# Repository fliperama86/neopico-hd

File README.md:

# NeoPico-HD

Digital video and audio capture with HDMI output for Neo Geo MVS arcade hardware using Raspberry Pi Pico 2 (RP2350B).

## Features

- **Native 240p HDMI output** at 60fps (via 480p line doubling for audio compatibility)
- **Experimental exact-clock 720p HDMI output** - the normal selector uses a 64.000 MHz, 1440x741 reduced-blanking raster at 59.979 Hz and centers the source at 3x scale
- **15-bit RGB + SHADOW/DARK capture** - 19-bit capture path includes SHADOW and DARK control lines
- **Pixel Conversion Modes** - Stable 32K-entry RGB LUT, plus an optional live and persistent `Digital`/`Analog` normal-color selector that remains separate from DARK/SHADOW processing
- **Translucent OSD Panel** - Enabled by default; game pixels under the black panel retain 12.5% brightness while text and menu colors remain opaque
- **Digital audio capture** from I2S bus (before DAC) with 48kHz HDMI output
- **Zero-overhead DMA video capture** - uses PIO + DMA with ping-pong buffering for perfect stability
- **PicoHDMI Output** - Powered by the [PicoHDMI](https://github.com/fliperama86/pico_hdmi) library for efficient, hardware-native TMDS encoding via RP2350 HSTX.

## Status

| Feature                 | Status                                     |
| ----------------------- | ------------------------------------------ |
| 480p HDMI video         | Working                                    |
| 720p HDMI video         | Experimental (exact-clock runtime selector mode) |
| 60fps capture           | Working                                    |
| RGB555 Digital path     | Working                                    |
| Live Colors selector    | Available whenever DARK/SHADOW is off (MVS builds) |
| SHADOW/DARK capture     | Working                                    |
| SHADOW/DARK conversion  | Experimental, default off; split-LUT hardware test showed bottom-screen pixel jitter |
| HDMI audio (48kHz)      | Working                                    |
| OSD Diagnostics         | Working                                    |
| Morhph4K, RetroTink 4K  | Tested                                     |
| Samsung Q80, Acer Pred. | Tested                                     |

## Hardware Requirements

- **Raspberry Pi Pico 2** - Must be RP2350**B** variant (48 GPIOs) for digital audio capture
- **Neo Geo MVS board** - Tested on MV1C
- **HDMI connector** wired to Pico GPIO

### Hardware Setup & Signal Integrity

To ensure clean audio and video capture, follow these best practices:

1.  **Common Ground**: A solid ground connection between the MVS board and the Pico is **mandatory**.
2.  **HDMI Power**: It is **absolutely mandatory** to have the HDMI connector properly powered with **+5V**. While some devices (like the Morph4K) may be forgiving, others (like the RetroTINK, TVs and monitors) will not pick up the signal without it.
3.  **Level Shifting**: Route all MVS -> Pico digital lines through proper **5V-to-3.3V level shifters**.
4.  **Clock Conditioning**: Keep **Schmitt-trigger conditioning** on PCLK and BCK for clean edges.
5.  **Power-Path Isolation**: Prevent back-feed between external 5V and USB 5V (ideal diode/power mux approach recommended).
6.  **Cable Separation**: Physically separate the I2S audio wires (GPIO 22-24 path) from the video wire bundle to avoid coupling.
7.  **Shielding**: Use a **GND-Signal-GND** pattern when using ribbon cables.

### Pin Configuration

#### Video Capture (Bank 1)

| Function   | GPIO       | Notes                |
| ---------- | ---------- | -------------------- |
| MVS CSYNC  | GPIO 27    | Composite sync       |
| MVS PCLK   | GPIO 28    | 6 MHz pixel clock    |
| MVS Blue   | GPIO 29-33 | B4-B0 (contiguous)   |
| MVS Green  | GPIO 34-38 | G4-G0 (contiguous)   |
| MVS Red    | GPIO 39-43 | R4-R0 (contiguous)   |
| MVS SHADOW | GPIO 44    | Shadow dimming       |
| MVS DARK   | GPIO 45    | Dark dimming control |

#### HSTX Output (Bank 0/1)

| Function | GPIO       |
| -------- | ---------- |
| TMDS CLK | GPIO 12-13 |
| TMDS D0  | GPIO 14-15 |
| TMDS D1  | GPIO 16-17 |
| TMDS D2  | GPIO 18-19 |

#### Audio Capture

| Function | GPIO    | MV1C Tap Point |
| -------- | ------- | -------------- |
| I2S DAT  | GPIO 22 | R91            |
| I2S WS   | GPIO 23 | R90            |
| I2S BCK  | GPIO 24 | R92            |

#### Controller OSD Inputs (MVS/AES)

| Controller input | GPIO |
| ---------------- | ---- |
| START / MENU     | GP0  |
| SELECT / BACK    | GP1  |
| DOWN             | GP2  |
| UP               | GP3  |

The inputs are active low and use weak internal pull-ups so untapped pins stay
idle. They are always enabled, on both MVS/AES and SNES builds (GP0-3 are
unused by SNES capture, so this is harmless there too).

## Prebuilt Firmware

GitHub Releases include ready-to-flash selector firmware. Each UF2 can switch
between 240p, 480p, and 720p from the reboot-based OSD resolution menu. The MVS
asset also includes persistent Audio and live-preview Colors menus. The optional
PC monitor modes are default-off and are not included in those release choices.
The selector's 720p entry uses the exact 64.000 MHz reduced-blanking timing;
because it is non-CTA and advertises VIC 0, sink compatibility still needs broad
testing.

| Asset | Capture | OSD choices |
| ----- | ------- | ----------- |
| `neopico_hd_mvs.uf2` | Neo Geo MVS/AES | Resolution, Audio, and Digital/Analog Colors |
| `neopico_hd_snes.uf2` | SNES | Resolution |

Matching ELF files and the `neopico-hd-jlcpcb.zip` fabrication package are also
attached to each release. Controller-driven AES OSD navigation is enabled in
both release assets (GP0-3 are unused by SNES capture).

## Building

Requires [Pico SDK](https://github.com/raspberrypi/pico-sdk) with `PICO_SDK_PATH` set.

```bash
# Build and flash
./flash

# Optional standalone HDMI/OSD self-test firmware
cmake -S . -B build_selftest -DNEOPICO_BUILD_SELFTEST=ON
cmake --build build_selftest --target neopico_selftest -j4

# Standard MVS build. Audio is always SELECTABLE (persistent Audio menu
# between the digital NEO-YSA2 tap and an external PCM1802 ADC) and the
# live persistent Colors selector (Digital/Analog normal-color, ignoring
# DARK/SHADOW) is available automatically since DARK/SHADOW defaults off.
cmake -S . -B build_mvs
cmake --build build_mvs --target neopico_hd -j4

# Separate DARK/SHADOW timing experiment. This path produced bottom-screen
# pixel jitter in hardware testing. Enabling it automatically compiles out
# the Colors selector (the two features share the same capture LUT machinery).
cmake -S . -B build_effects \
  -DNEOPICO_ENABLE_DARK_SHADOW=ON \
  -DNEOPICO_MVS_EFFECT_MODEL=MISTER
cmake --build build_effects --target neopico_hd -j4

# Digital-only register-processing experiment. This replaces the split effect
# LUT with RBIT, bitfield, saturating DARK, and packed SHADOW operations. It is
# default off and must be hardware-validated before use in release firmware.
cmake -S . -B build_effects_processing \
  -DNEOPICO_COPY_TO_RAM=ON \
  -DNEOPICO_ENABLE_DARK_SHADOW=ON \
  -DNEOPICO_MVS_DIGITAL_EFFECT_PROCESSING=ON \
  -DNEOPICO_MVS_EFFECT_MODEL=MISTER
cmake --build build_effects_processing --target neopico_hd -j4
```

## Architecture

```
Core 0: Video Capture               Core 1: Audio Pipeline + HSTX
+--------------------------+       +--------------------------+
| Video: PIO1 -> DMA (PP)  |       | Audio: PIO2 -> processing|
| Conv: 32K LUT (dual opt) |       | [ PicoHDMI Library ]     |
| Main loop: Control       |       | - 640x480 @ 60Hz         |
| Heartbeat LED            |       | - HDMI Data Islands      |
+--------------------------+       +--------------------------+
          |                        +--------------------------+
          |                                   |
          +--------- framebuf ----------------+
                  (320x240 RGB565)
```

### PicoHDMI Library Integration

The project leverages the [PicoHDMI](https://github.com/fliperama86/pico_hdmi) library (found in `lib/pico_hdmi`) to interface with the RP2350's HSTX peripheral. This library provides the high-performance TMDS encoding and Data Island management required for stable HDMI output.

- **Dedicated Output Core**: To ensure rock-solid HDMI timing (exactly 800 cycles per line), the library runs its main loop on **Core 1**. This isolates the high-priority TMDS serialization from the video capture logic on Core 0.
- **Zero-Latency Scaling**: We use the library's `video_output_set_scanline_callback()` to implement a scanline doubler. This performs 2x vertical upscaling (240p to 480p) on-the-fly as pixels are streamed to the HSTX, avoiding the need for a full 480p framebuffer.
- **HDMI Audio Injection**: Audio data is integrated via the library's Data Island queue (`hstx_di_queue`). The audio subsystem pushes TERC4-encoded packets into this queue, which the library then automatically injects during the horizontal blanking intervals.
- **Frame Synchronization**: A VSYNC callback is used to keep the video capture ring buffer and the HDMI output in perfect sync, minimizing latency and preventing screen tearing.

## Documentation

- **[System Architecture](docs/ARCHITECTURE.md)**: High-level design, core partitioning, and the closed-loop audio sync.
- **[Video Implementation](docs/MVS_MV1C_DIGITAL_VIDEO.md)**: Tap points, signal logic, and PIO capture.
- **[Audio Implementation](docs/MVS_MV1C_DIGITAL_AUDIO.md)**: I2S format, ASRC strategy, and drift control.
- **[Standalone PCM1802 USB Capture](docs/PCM1802_USB_CAPTURE.md)**: Raw ADC diagnostic firmware and host capture tool.
- **[HSTX & HDMI](docs/HSTX_IMPLEMENTATION.md)**: Output timing, TMDS, and Data Islands.
- **[OSD](docs/OSD_IMPLEMENTATION.md)**: On-Screen Display rendering.
- **[Reboot Resolution Switching](docs/REBOOT_RESOLUTION_SWITCHING.md)**: Reboot selector modes.
- **[720p Samsung Game Mode Investigation](docs/720P_SAMSUNG_GAME_MODE_INVESTIGATION.md)**: Current findings on Samsung Game Mode 720p glitches.
- **[Known Issues](docs/KNOWN_ISSUES.md)**: Current limitations and compatibility notes.

## Architecture Highlights

- **Dual-Core Design**: Dedicated cores for Video Capture (Core 0) and HDMI Output (Core 1).
- **Closed-Loop Audio Sync**: Software-defined feedback loop effectively "genlocks" the MVS audio to the HDMI clock, preventing drift and glitches without an FPGA.
- **Zero-Lag**: Scanline-doubling architecture with no framebuffer delay.

## Installation

Unlicense

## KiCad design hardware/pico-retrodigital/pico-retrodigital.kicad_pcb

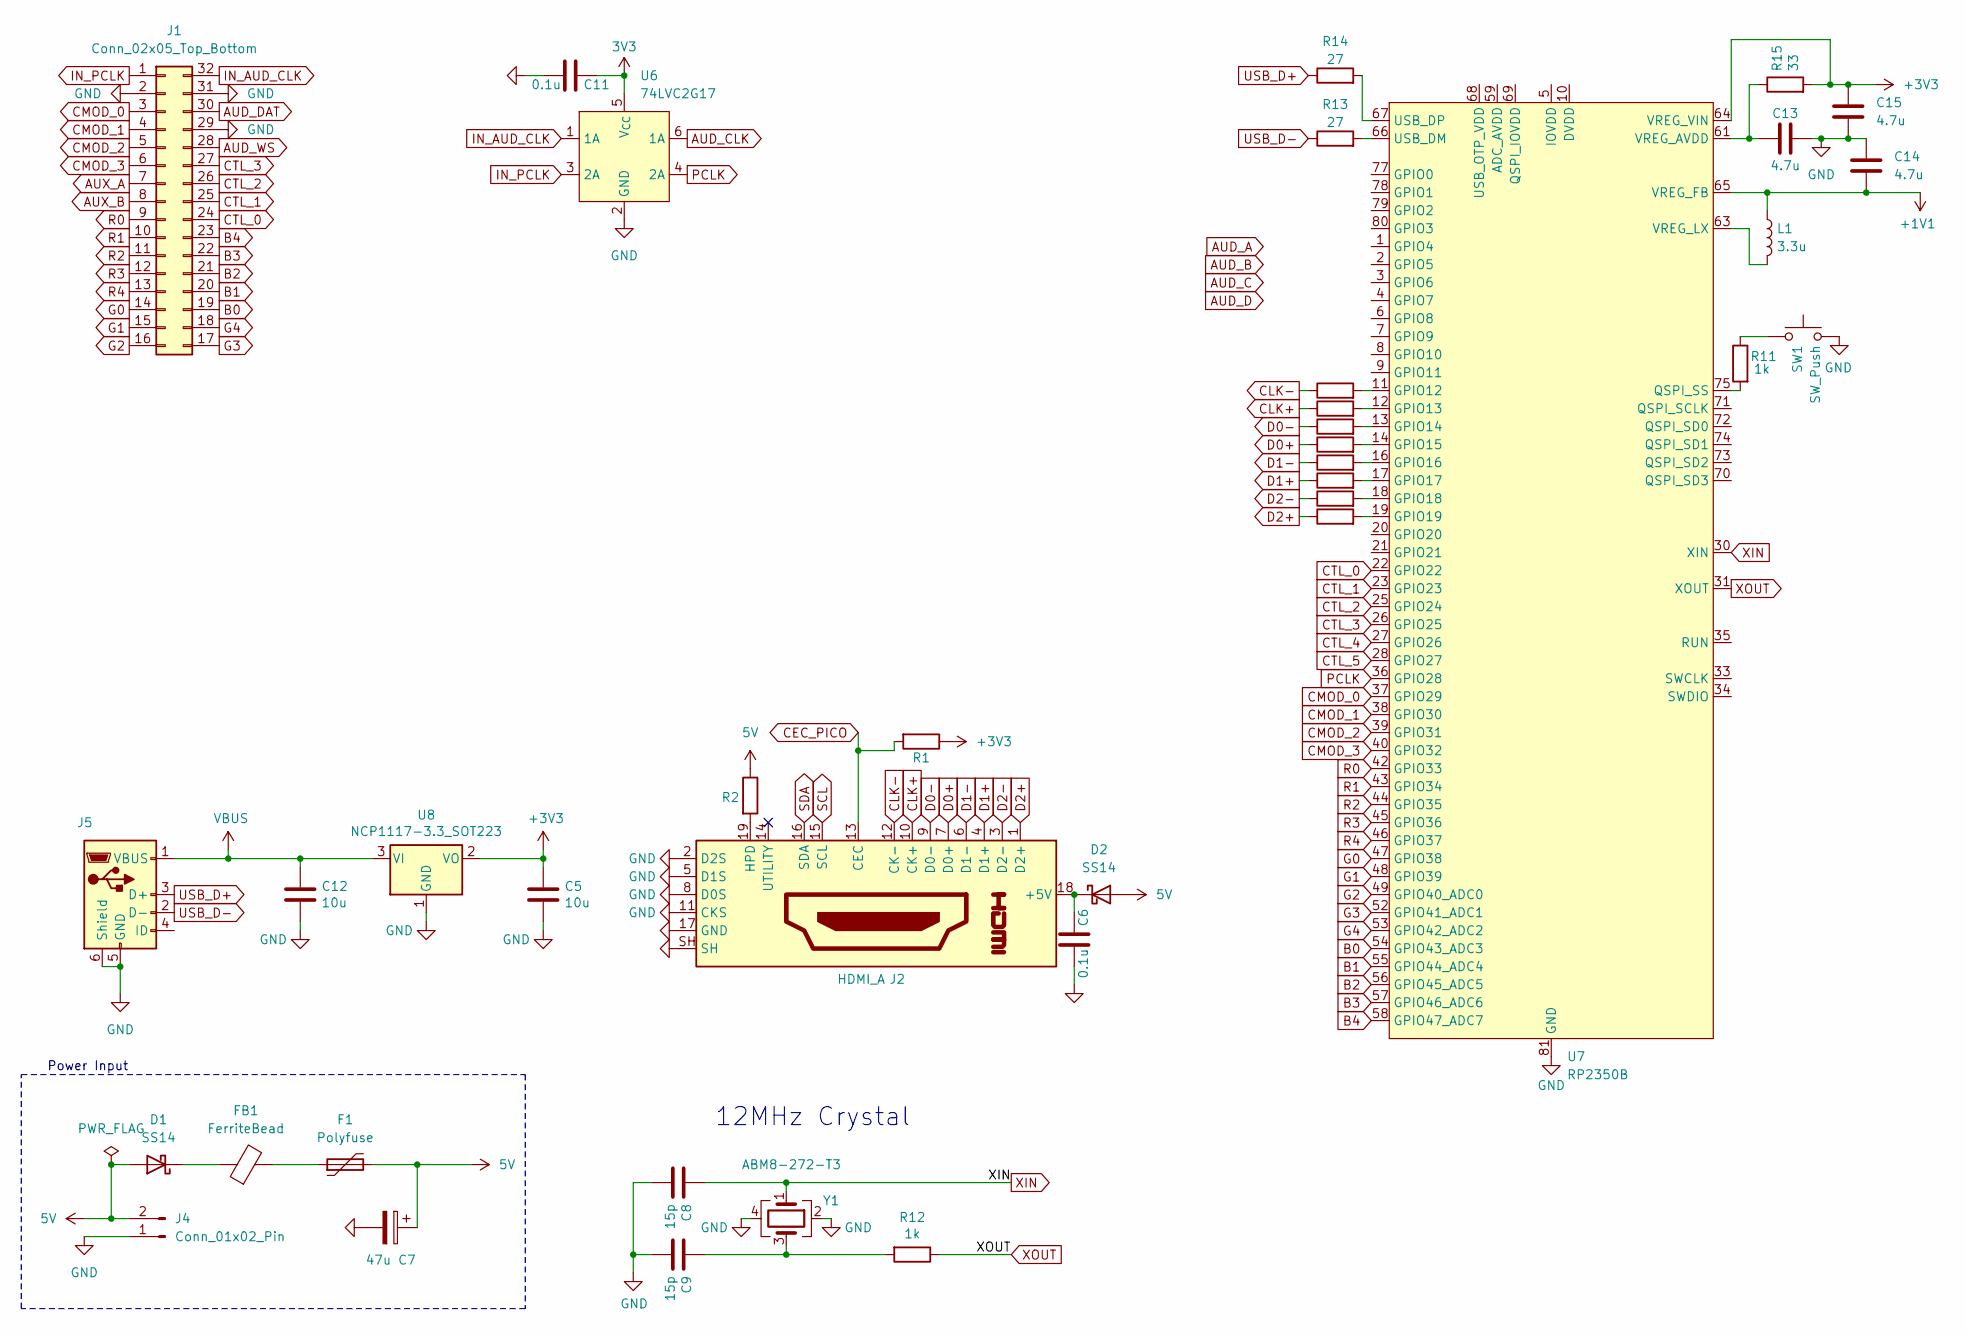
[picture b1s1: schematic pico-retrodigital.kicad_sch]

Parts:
C5, C12: 10u; C_0402_1005Metric
C6, C11: 0.1u; C_0603_1608Metric
C7: 47u; CP_Radial_D4.0mm_P2.00mm
C8, C9: 15p; C_0402_1005Metric
C13: 4.7u; C_0402_1005Metric
C14, C15: 4.7u; C_0402_1005Metric_small_pads
D1, D2: SS14; D_0603_1608Metric
F1: Polyfuse; C_0603_1608Metric
FB1: FerriteBead; C_0603_1608Metric
J1: Conn_02x05_Top_Bottom; TE_3-1734839-2_1x32-1MP_P0.5mm_Horizontal
J2: HDMI_A; HDMI_A_Molex_208658-1001_Horizontal
J4: Conn_01x02_Pin; PinHeader_1x02_P2.54mm_Vertical
J5: USB_C; USB_Micro-B_Amphenol_10103594-0001LF_Horizontal
L1: 3.3u; L_pol_2016
R1: 27K; R_0603_1608Metric
R2: 10K; R_0603_1608Metric
R3, R4, R5, R6, R7, R8, R9, R10: 220; R_0201_0603Metric
R11, R12: 1k; R_0402_1005Metric
R13, R14: 27; R_0402_1005Metric
R15: 33; R_0402_1005Metric
SW1: SW_Push; SW_Push_1P1T_NO_Vertical_Wuerth_434133025816
U6: 74LVC2G17; SOT-23-6
U7: RP2350B; QFN-80-1EP_10x10mm_P0.4mm_EP3.4x3.4mm_ThermalVias
U8: NCP1117-3.3_SOT223; SOT-223-3_TabPin2
Y1: ABM8-272-T3; Crystal_SMD_3225-4Pin_3.2x2.5mm

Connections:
3V3: C11.1, U6.5 (V_{CC})
5V: C7.1, D1.2 (A), D2.2 (A), F1.2, J4.2, R2.1
+1V1: C14.2, L1.1, U7.65 (VREG_FB)
+3V3: C5.1, C15.1, R1.1, R15.2, U7.64 (VREG_VIN), U8.2 (VO); also elsewhere on the board
AUD_CLK: U6.6 (1A)
AUD_DAT: J1.30
AUD_WS: J1.28
AUX_A: J1.7
AUX_B: J1.8
B0: J1.19, U7.54 (GPIO43_ADC3)
B1: J1.20, U7.55 (GPIO44_ADC4)
B2: J1.21, U7.56 (GPIO45_ADC5)
B3: J1.22, U7.57 (GPIO46_ADC6)
B4: J1.23, U7.58 (GPIO47_ADC7)
CEC_PICO: J2.13 (CEC), R1.2
CLK+: J2.10 (CK+), R5.1
CLK-: J2.12 (CK-), R4.1
CMOD_0: J1.3, U7.37 (GPIO29)
CMOD_1: J1.4, U7.38 (GPIO30)
CMOD_2: J1.5, U7.39 (GPIO31)
CMOD_3: J1.6, U7.40 (GPIO32)
CTL_0: J1.24, U7.22 (GPIO22)
CTL_1: J1.25, U7.23 (GPIO23)
CTL_2: J1.26, U7.25 (GPIO24)
CTL_3: J1.27, U7.26 (GPIO25)
CTL_4: U7.27 (GPIO26)
CTL_5: U7.28 (GPIO27)
D0+: J2.7 (D0+), R6.1
D0-: J2.9 (D0-), R3.1
D1+: J2.4 (D1+), R8.1
D1-: J2.6 (D1-), R7.1
D2+: J2.1 (D2+), R10.1
D2-: J2.3 (D2-), R9.1
G0: J1.14, U7.47 (GPIO38)
G1: J1.15, U7.48 (GPIO39)
G2: J1.16, U7.49 (GPIO40_ADC0)
G3: J1.17, U7.52 (GPIO41_ADC1)
G4: J1.18, U7.53 (GPIO42_ADC2)
GND: C5.2, C6.2, C7.2, C8.2, C9.2, C11.2, C12.2, C13.2, C14.1, C15.2, J1.2, J1.29, J1.31, J2.2 (D2S), J2.5 (D1S), J2.8 (D0S), J2.11 (CKS), J2.17 (GND), J2.SH, J4.1, J5.5 (GND), J5.6 (Shield), SW1.1, U6.2 (GND), U7.62 (VREG_PGND), U7.81 (GND), U8.1 (GND), Y1.2, Y1.4; also elsewhere on the board
IN_AUD_CLK: J1.32, U6.1 (1A)
IN_PCLK: J1.1, U6.3 (2A)
unnamed: C9.1, R12.2, Y1.3
unnamed: D1.1 (K), FB1.1
unnamed: C6.1, D2.1 (K), J2.18 (+5V)
unnamed: F1.1, FB1.2
unnamed: J2.19 (HPD), R2.2
unnamed: R11.1, SW1.2
unnamed: U7.10 (DVDD), U7.32 (DVDD), U7.51 (DVDD)
unnamed: R4.2, U7.11 (GPIO12)
unnamed: R5.2, U7.12 (GPIO13)
unnamed: R3.2, U7.13 (GPIO14)
unnamed: R6.2, U7.14 (GPIO15)
unnamed: R7.2, U7.16 (GPIO16)
unnamed: R8.2, U7.17 (GPIO17)
unnamed: R9.2, U7.18 (GPIO18)
unnamed: R10.2, U7.19 (GPIO19)
unnamed: U7.5 (IOVDD), U7.15 (IOVDD), U7.24 (IOVDD), U7.29 (IOVDD), U7.41 (IOVDD), U7.50 (IOVDD), U7.60 (IOVDD), U7.76 (IOVDD)
unnamed: R11.2, U7.75 (QSPI_SS)
unnamed: R13.2, U7.66 (USB_DM)
unnamed: R14.2, U7.67 (USB_DP)
unnamed: C13.1, R15.1, U7.61 (VREG_AVDD)
unnamed: L1.2, U7.63 (VREG_LX)
PCLK: U6.4 (2A), U7.36 (GPIO28)
R0: J1.9, U7.42 (GPIO33)
R1: J1.10, U7.43 (GPIO34)
R2: J1.11, U7.44 (GPIO35)
R3: J1.12, U7.45 (GPIO36)
R4: J1.13, U7.46 (GPIO37)
SCL: J2.15 (SCL)
SDA: J2.16 (SDA)
USB_D+: J5.3 (D+), R14.1
USB_D-: J5.2 (D-), R13.1
VBUS: C12.1, J5.1 (VBUS), U8.3 (VI)
XIN: C8.1, U7.30 (XIN), Y1.1
XOUT: R12.1, U7.31 (XOUT)

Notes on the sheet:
Power Input
12MHz Crystal

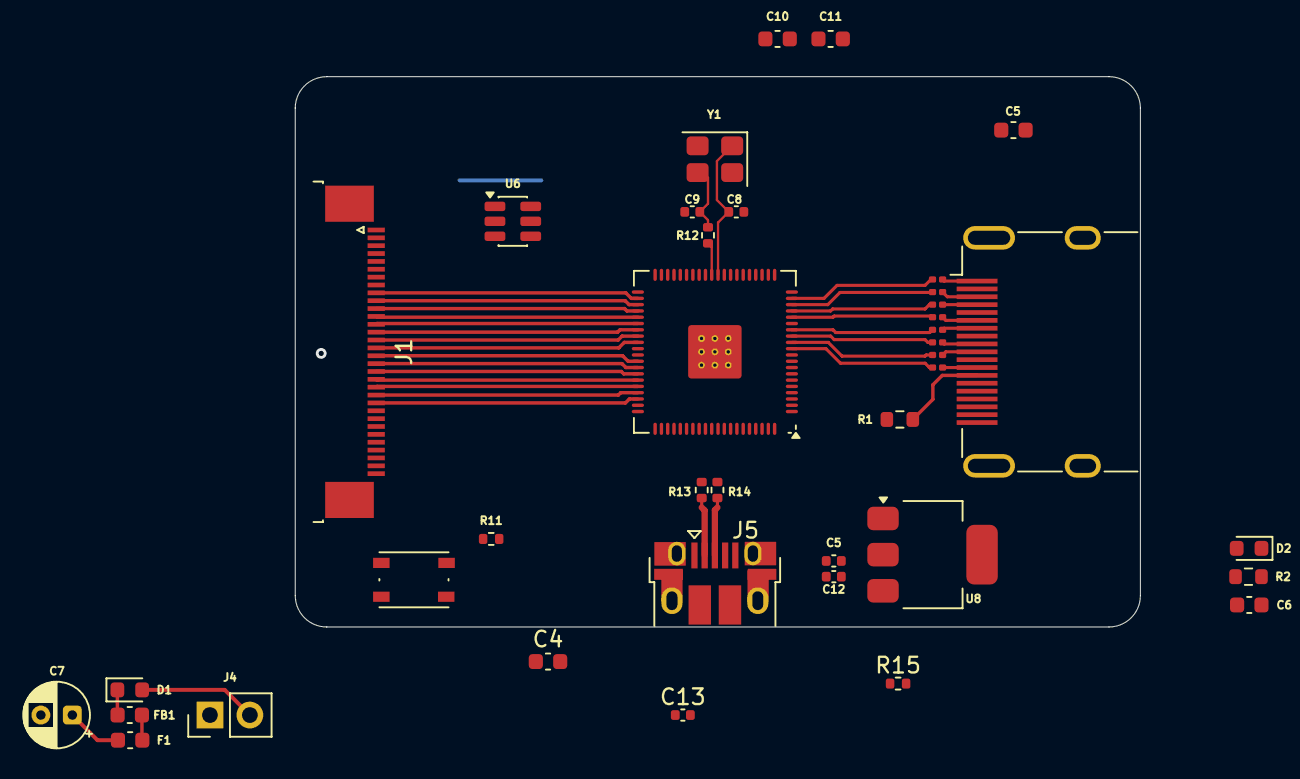
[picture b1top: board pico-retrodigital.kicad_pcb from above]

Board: 2 copper layers, 53.8 x 35.0 mm, 39 parts (0 on the bottom side), 64 nets.

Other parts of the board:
C4, C10: 0.1u; C_0603_1608Metric
C5#2: 10u; C_0402_1005Metric

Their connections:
+3V3: C4.1, C5#2.1, C10.1; also elsewhere on the board
GND: C4.2, C5#2.2, C10.2; also elsewhere on the board

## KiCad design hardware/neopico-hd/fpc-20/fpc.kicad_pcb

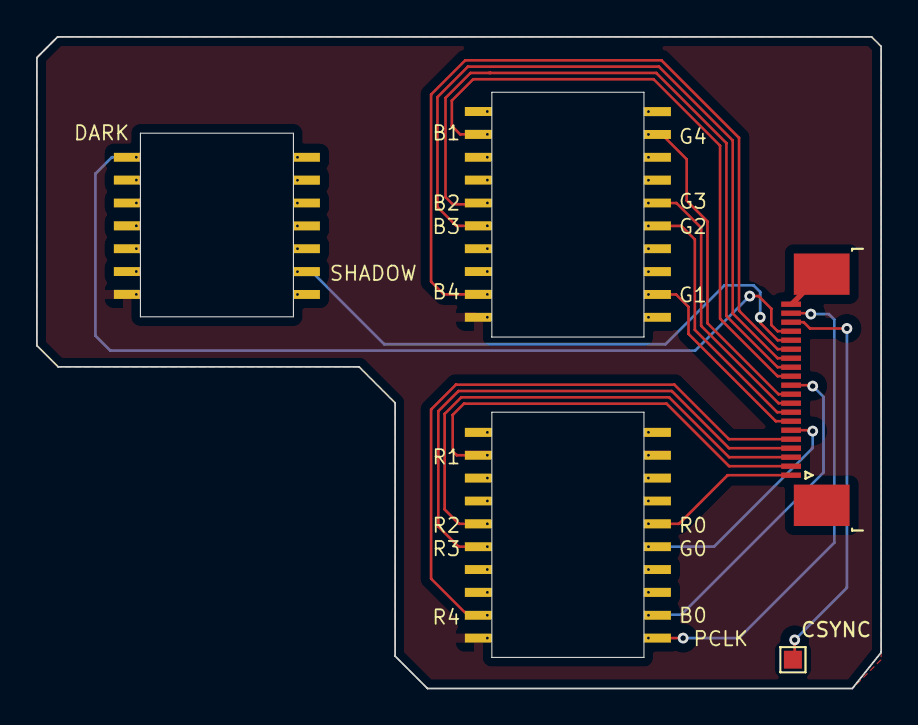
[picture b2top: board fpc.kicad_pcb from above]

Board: 2 copper layers, 46.9 x 36.2 mm, 3 parts (0 on the bottom side), 20 nets.

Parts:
CSYNC_PAD: TestPoint_Pad_1.0x1.0mm
J1: Conn_02x27_Pin; MVS_Color_Latches
J2: Conn_01x20_Pin; TE_2-1734839-0_1x20-1MP_P0.5mm_Horizontal

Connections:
B0: J1.32, J2.11
B1: J1.2, J2.12
B2: J1.5, J2.13
B3: J1.6, J2.14
B4: J1.9, J2.15
CSYNC: CSYNC_PAD.1, J2.18
DARK: J1.41, J2.17
G0: J1.35, J2.6
G1: J1.12, J2.7
G2: J1.15, J2.8
G3: J1.16, J2.9
G4: J1.19, J2.10
GND: J1.10, J1.30, J1.47, J2.20
PCLK: J1.31, J2.19
R0: J1.36, J2.1
R1: J1.22, J2.2
R2: J1.25, J2.3
R3: J1.26, J2.4
R4: J1.29, J2.5
SHADOW: J1.53, J2.16

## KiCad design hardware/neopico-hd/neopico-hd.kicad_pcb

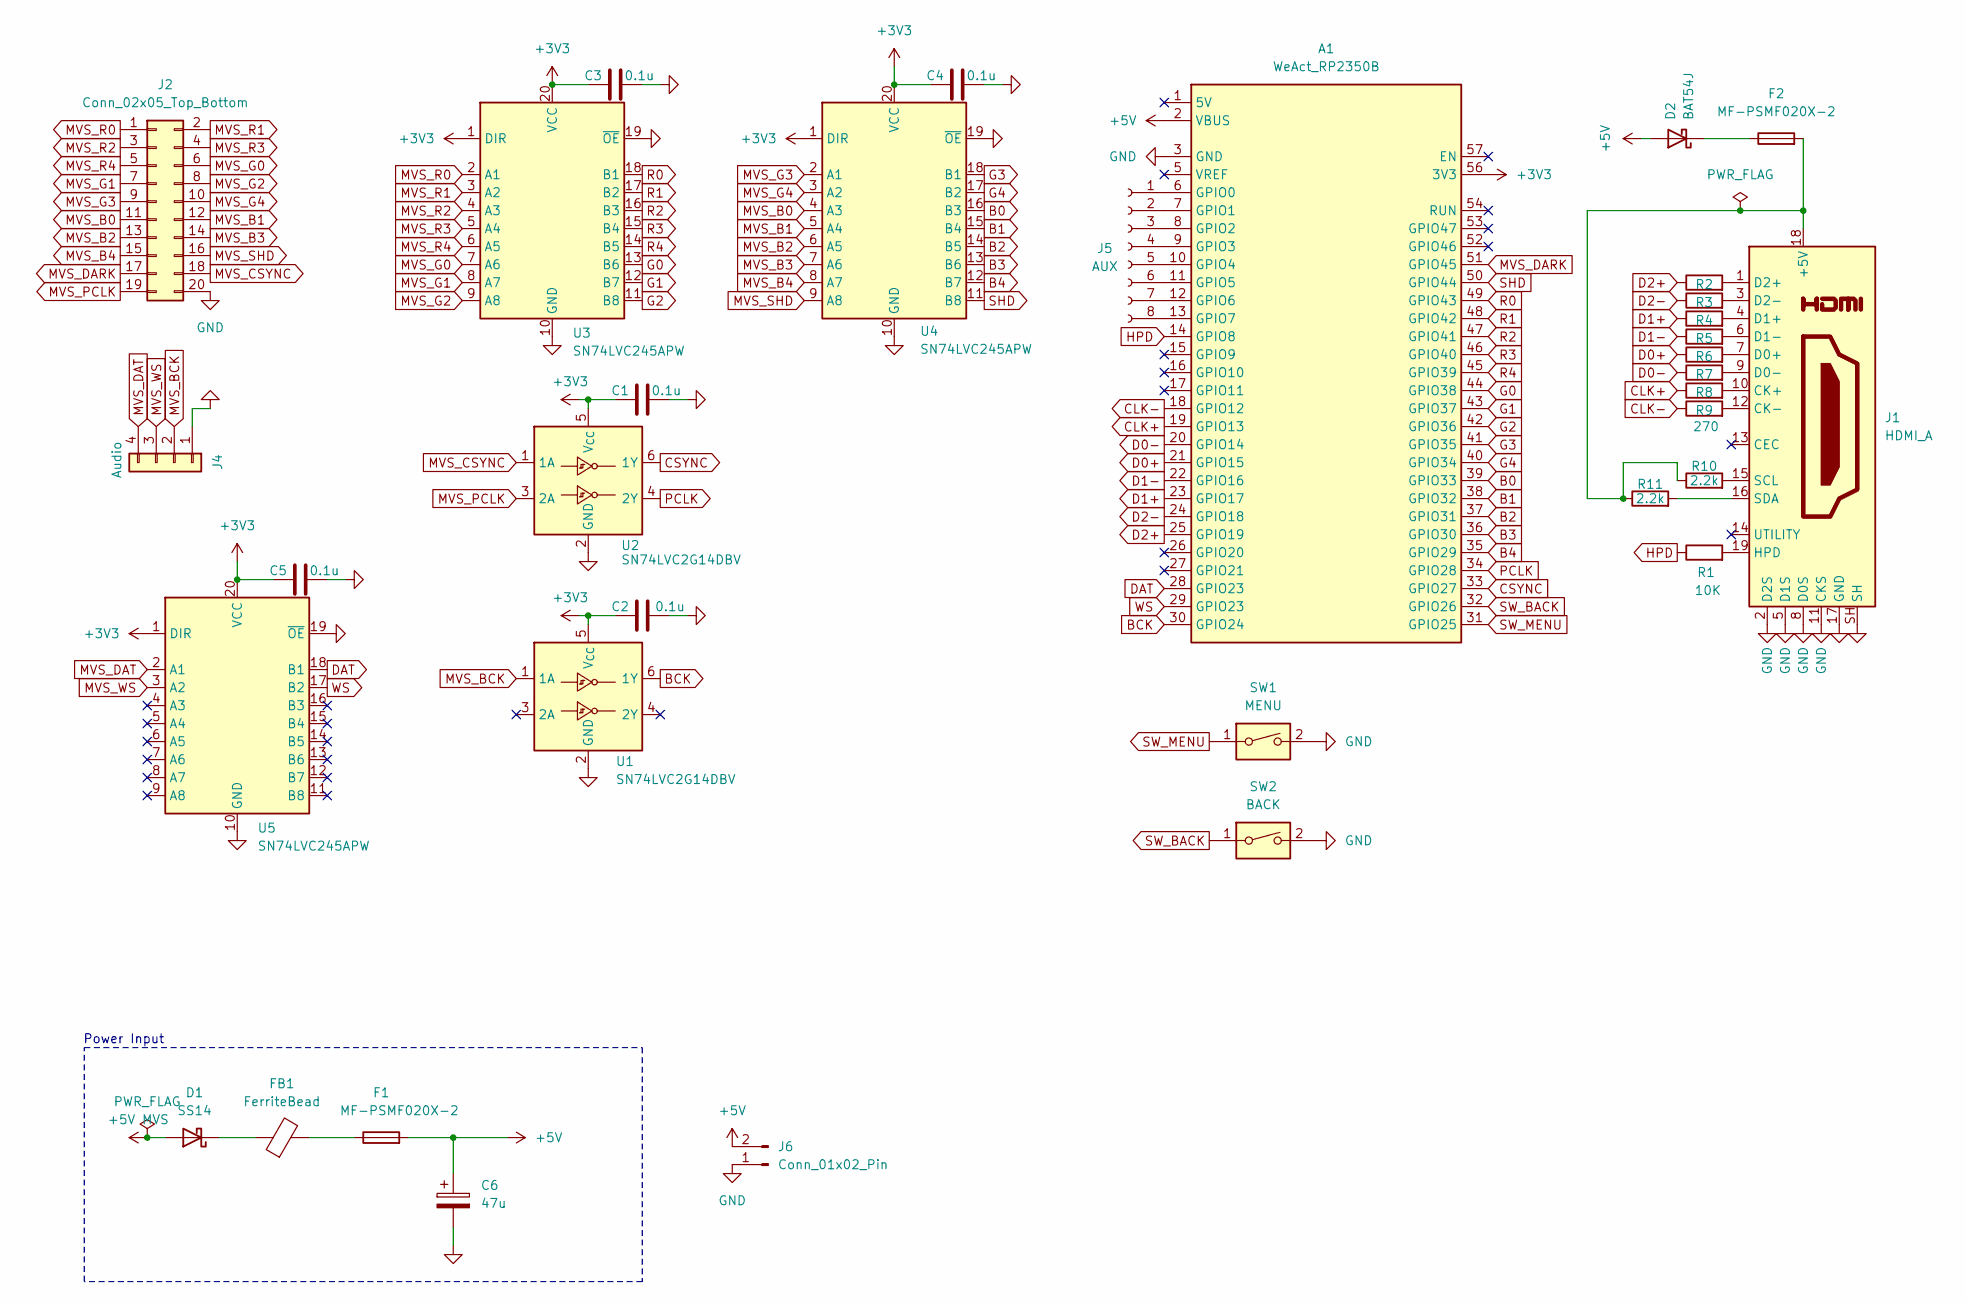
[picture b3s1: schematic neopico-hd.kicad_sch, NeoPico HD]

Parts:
A1: WeAct_RP2350B
C1, C2, C3, C4, C5: 0.1u; C_0805_2012Metric_Pad1.18x1.45mm_HandSolder; LCSC C1711
C6: 47u; CP_Elec_6.3x5.4_Nichicon; LCSC C7094687
D1: SS14; D_SMA; LCSC C83852
D2: BAT54J; D_SOD-323F; LCSC C86299
F1: MF-PSMF020X-2; C_0805_2012Metric; LCSC C89657
F2: MF-PSMF020X-2; Fuse_0805_2012Metric; LCSC C89657
FB1: FerriteBead; C_0805_2012Metric; LCSC C76815
J1: HDMI_A; HDMI_A_Molex_208658-1001_Horizontal; LCSC C111617
J2: Conn_02x05_Top_Bottom; IDC-Header_2x10_P2.54mm_Vertical
J4: Audio; JST_XA_B04B-XASK-1_1x04_P2.50mm_Vertical
J5: AUX; PinHeader_2x04_P2.54mm_Vertical
J6: Conn_01x02_Pin; PinHeader_1x02_P2.54mm_Vertical
R1: 10K; R_0603_1608Metric; LCSC C98220
R2, R3, R4, R5, R6, R7, R8, R9: 270; R_0402_1005Metric; LCSC C163474
R10, R11: 2.2k; R_0603_1608Metric; LCSC C114662
SW1: MENU; SW_SPST_CK_KXT3
SW2: BACK; SW_SPST_CK_KXT3
U1, U2: SN74LVC2G14DBV; SOT-23-6; LCSC C12401
U3, U4, U5: SN74LVC245APW; TSSOP-20_4.4x6.5mm_P0.65mm; LCSC C7848

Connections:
+3V3: A1.55 (3V3), A1.56 (3V3), C1.1, C2.1, C3.1, C4.1, C5.1, U1.5 (V_{CC}), U2.5 (V_{CC}), U3.1 (DIR), U3.20 (VCC), U4.1 (DIR), U4.20 (VCC), U5.1 (DIR), U5.20 (VCC); also elsewhere on the board
+5V: A1.2 (VBUS), C6.1, D2.2 (A), F1.2, J6.2
+5V MVS: D1.2 (A); also elsewhere on the board
B0: A1.39 (GPIO33), U4.16 (B3)
B1: A1.38 (GPIO32), U4.15 (B4)
B2: A1.37 (GPIO31), U4.14 (B5)
B3: A1.36 (GPIO30), U4.13 (B6)
B4: A1.35 (GPIO29), U4.12 (B7)
BCK: A1.30 (GPIO24), U1.6 (1Y)
CLK+: A1.19 (GPIO13), R8.1
CLK-: A1.18 (GPIO12), R9.1
CSYNC: A1.33 (GPIO27), U2.6 (1Y)
D0+: A1.21 (GPIO15), R6.1
D0-: A1.20 (GPIO14), R7.1
D1+: A1.23 (GPIO17), R4.1
D1-: A1.22 (GPIO16), R5.1
D2+: A1.25 (GPIO19), R2.1
D2-: A1.24 (GPIO18), R3.1
DAT: A1.28 (GPIO23), U5.18 (B1)
G0: A1.44 (GPIO38), U3.13 (B6)
G1: A1.43 (GPIO37), U3.12 (B7)
G2: A1.42 (GPIO36), U3.11 (B8)
G3: A1.41 (GPIO35), U4.18 (B1)
G4: A1.40 (GPIO34), U4.17 (B2)
GND: A1.3 (GND), A1.4 (GND), A1.58 (GND), A1.59 (GND), A1.60 (GND), C1.2, C2.2, C3.2, C4.2, C5.2, C6.2, J1.2 (D2S), J1.5 (D1S), J1.8 (D0S), J1.11 (CKS), J1.17 (GND), J1.SH, J2.20, J4.1, J6.1, SW1.2, SW2.2, U1.2 (GND), U2.2 (GND), U3.10 (GND), U3.19 (~OE), U4.10 (GND), U4.19 (~OE), U5.10 (GND), U5.19 (~OE); also elsewhere on the board
HPD: A1.14 (GPIO8), R1.1
MVS_B0: J2.11, U4.4 (A3)
MVS_B1: J2.12, U4.5 (A4)
MVS_B2: J2.13, U4.6 (A5)
MVS_B3: J2.14, U4.7 (A6)
MVS_B4: J2.15, U4.8 (A7)
MVS_BCK: J4.2, U1.1 (1A)
MVS_CSYNC: J2.18, U2.1 (1A)
MVS_DARK: A1.51 (GPIO45), J2.17
MVS_DAT: J4.4, U5.2 (A1)
MVS_G0: J2.6, U3.7 (A6)
MVS_G1: J2.7, U3.8 (A7)
MVS_G2: J2.8, U3.9 (A8)
MVS_G3: J2.9, U4.2 (A1)
MVS_G4: J2.10, U4.3 (A2)
MVS_PCLK: J2.19, U2.3 (2A)
MVS_R0: J2.1, U3.2 (A1)
MVS_R1: J2.2, U3.3 (A2)
MVS_R2: J2.3, U3.4 (A3)
MVS_R3: J2.4, U3.5 (A4)
MVS_R4: J2.5, U3.6 (A5)
MVS_SHD: J2.16, U4.9 (A8)
MVS_WS: J4.3, U5.3 (A2)
unnamed: A1.6 (GPIO0), J5.1
unnamed: A1.7 (GPIO1), J5.2
unnamed: A1.8 (GPIO2), J5.3
unnamed: A1.9 (GPIO3), J5.4
unnamed: A1.10 (GPIO4), J5.5
unnamed: A1.11 (GPIO5), J5.6
unnamed: A1.12 (GPIO6), J5.7
unnamed: A1.13 (GPIO7), J5.8
unnamed: D1.1 (K), FB1.1
unnamed: D2.1 (K), F2.1
unnamed: F1.1, FB1.2
unnamed: F2.2, J1.18 (+5V), R10.1, R11.1
unnamed: J1.10 (CK+), R8.2
unnamed: J1.12 (CK-), R9.2
unnamed: J1.7 (D0+), R6.2
unnamed: J1.9 (D0-), R7.2
unnamed: J1.4 (D1+), R4.2
unnamed: J1.6 (D1-), R5.2
unnamed: J1.1 (D2+), R2.2
unnamed: J1.3 (D2-), R3.2
unnamed: J1.19 (HPD), R1.2
unnamed: J1.15 (SCL), R10.2
unnamed: J1.16 (SDA), R11.2
PCLK: A1.34 (GPIO28), U2.4 (2Y)
R0: A1.49 (GPIO43), U3.18 (B1)
R1: A1.48 (GPIO42), U3.17 (B2)
R2: A1.47 (GPIO41), U3.16 (B3)
R3: A1.46 (GPIO40), U3.15 (B4)
R4: A1.45 (GPIO39), U3.14 (B5)
SHD: A1.50 (GPIO44), U4.11 (B8)
SW_BACK: A1.32 (GPIO26), SW2.1
SW_MENU: A1.31 (GPIO25), SW1.1
WS: A1.29 (GPIO23), U5.17 (B2)

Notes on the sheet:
Power Input

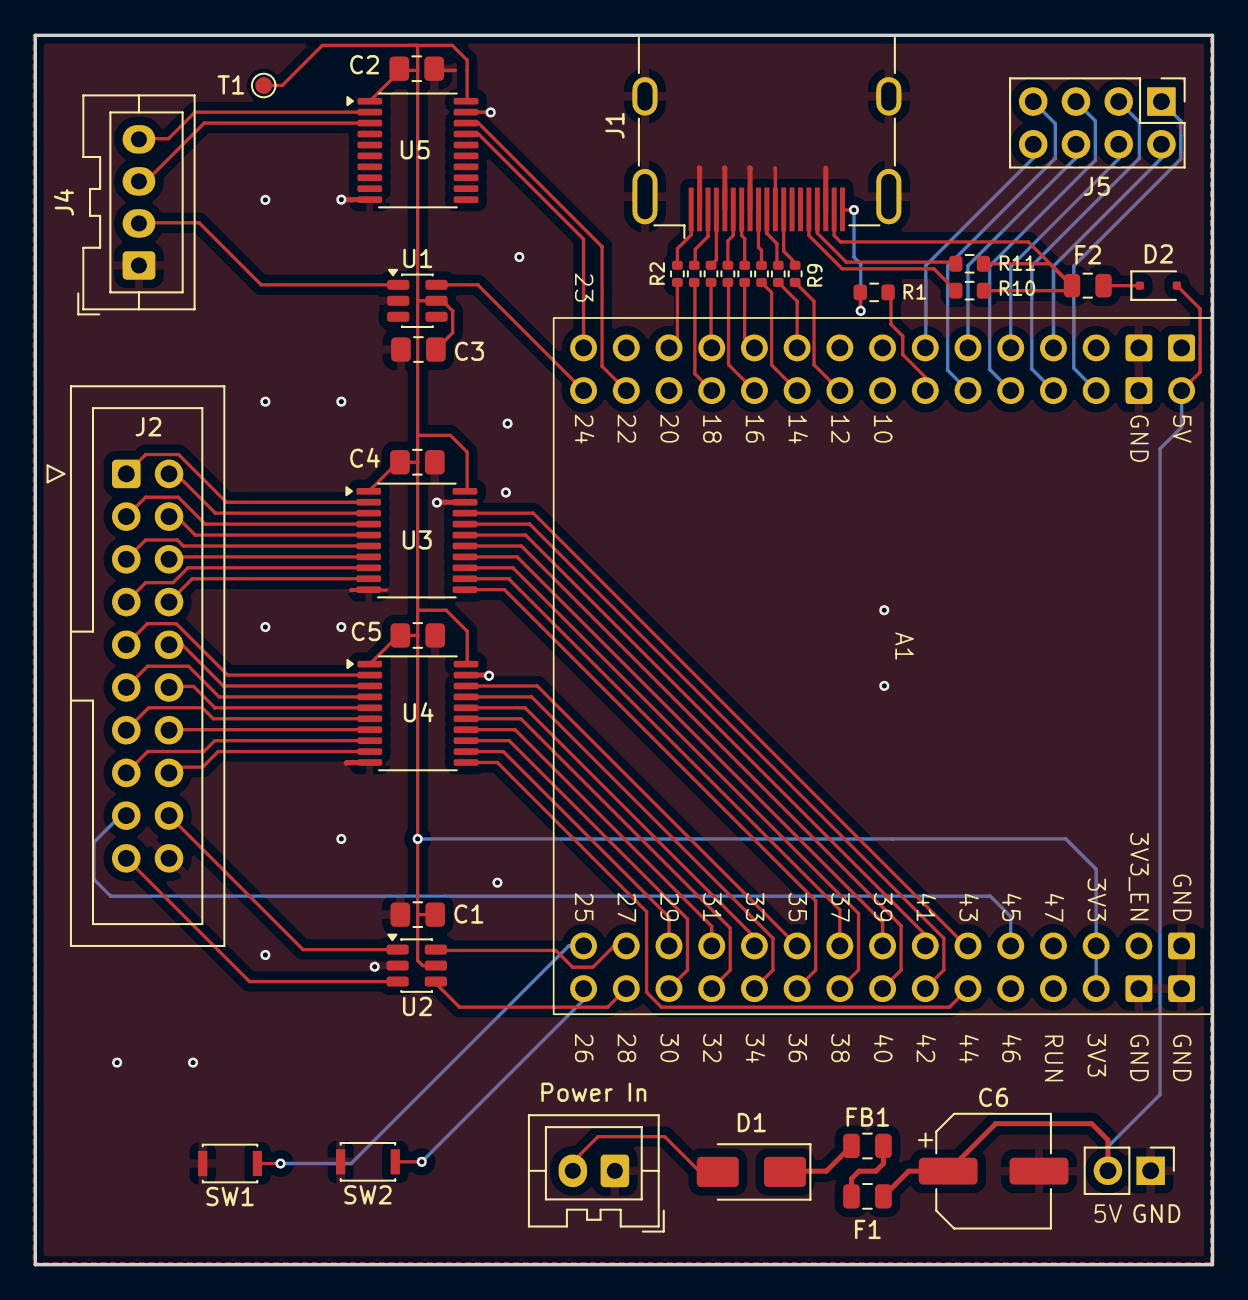
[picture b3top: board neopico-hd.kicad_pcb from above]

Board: 2 copper layers, 70.0 x 73.1 mm, 37 parts (0 on the bottom side), 81 nets.

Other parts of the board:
Power In: JST_XA_B02B-XASK-1_1x02_P2.50mm_Vertical
T1: TestPoint_Pad_D1.0mm

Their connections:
+3V3: T1.1; also elsewhere on the board
+5V MVS: Power In.2; also elsewhere on the board
GND: Power In.1; also elsewhere on the board

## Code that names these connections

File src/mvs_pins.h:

/**
 * NeoPico-HD MVS Pin Configuration
 *
 * This file contains all MVS capture, I2S audio, and OSD control pins.
 * These are specific to the NeoPico-HD firmware and hardware layout.
 */

#ifndef MVS_PINS_H
#define MVS_PINS_H

// =============================================================================
// MVS Video Input Pins - GP27-45 CONTIGUOUS LAYOUT
// =============================================================================
// Captures RGB555 + SHADOW + DARK from Neo Geo MVS.
//
// 19-pin capture window: GP27 (LSB) through GP45 (MSB).
//
// Pin mapping (LSB to MSB in captured word):
//   Bit 0:      GP27 (CSYNC)
//   Bit 1:      GP28 (PCLK)
//   Bits 2-6:   GP29-33 (Blue B4-B0, contiguous)
//   Bits 7-11:  GP34-38 (Green G4-G0, contiguous)
//   Bits 12-16: GP39-43 (Red R4-R0, contiguous)
//   Bit 17:     GP44 (SHADOW)
//   Bit 18:     GP45 (DARK)
//
// With PIO GPIOBASE=16, pin index N = GP(N+16). So IN_BASE=11 → GP27.

#define PIN_MVS_CSYNC 27 // Composite sync (position 0 in capture word)
#define PIN_MVS_PCLK 28  // Pixel clock (6 MHz, position 1)
#define PIN_MVS_BASE 27  // Base pin - capture GP27-45 (19 pins), CSYNC first

// Blue channel (B4-B0) - CONTIGUOUS at bits 2-6
#define PIN_MVS_B4 29
#define PIN_MVS_B3 30
#define PIN_MVS_B2 31
#define PIN_MVS_B1 32
#define PIN_MVS_B0 33

// Green channel (G4-G0) - CONTIGUOUS at bits 7-11
#define PIN_MVS_G4 34
#define PIN_MVS_G3 35
#define PIN_MVS_G2 36
#define PIN_MVS_G1 37
#define PIN_MVS_G0 38

// Red channel (R4-R0) - CONTIGUOUS at bits 12-16
#define PIN_MVS_R4 39
#define PIN_MVS_R3 40
#define PIN_MVS_R2 41
#define PIN_MVS_R1 42
#define PIN_MVS_R0 43

// Special effects
#define PIN_MVS_SHADOW 44 // Bit 17
#define PIN_MVS_DARK 45   // Bit 18

#define MVS_CAPTURE_PIN_LAST PIN_MVS_DARK
#define MVS_CAPTURE_BITS 19

// =============================================================================
// I2S Audio Input Pins (DAT=GP22, WS=GP23, BCK=GP24)
// =============================================================================
// MV1C: NEO-YSA2 digital tap (right-justified, ~55.5kHz)
// PCM1802: ADC I2S output (standard I2S, 48kHz with 12.288MHz SCKI)
// Same GPIOs for both — pin order constrained by PIO `wait pin N`
#define PIN_I2S_DAT 22 // I2S data (DOUT on PCM1802)
#define PIN_I2S_WS 23  // I2S word select (LRCK on PCM1802)
#define PIN_I2S_BCK 24 // I2S bit clock (BCK on PCM1802)

// =============================================================================
// OSD Control (Direct Buttons)
// =============================================================================
// Custom PCB (WeAct RP2350B): SW_MENU=GP25, SW_BACK=GP26. Change if different.
#define PIN_OSD_BTN_MENU 25 // Menu / Select Button
#define PIN_OSD_BTN_BACK 26 // Back / Cycle Button

#endif // MVS_PINS_H

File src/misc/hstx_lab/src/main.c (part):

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 *     GPIO 18: D2N     GPIO 19: D2P  (Lane 2 - Red)
 *
 * MVS Capture (GPIO 25-43 via PIO1):
 *     GPIO 25: PCLK, GPIO 26-30: Red, GPIO 31-35: Green,
 *     GPIO 36-40: Blue, GPIO 41: DARK, GPIO 42: SHADOW, GPIO 43: CSYNC
 *
 * Audio: 48kHz stereo via HDMI Data Islands (test tone)
 *
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
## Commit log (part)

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2025-11-28 First load
2025-11-28 Update docs
2025-11-28 Remove old code
2025-11-29 Phase 5 complete: 4-bit RGB capture working perfectly!
    Major achievement: Solved PIO autopush alignment problem using 4-bit capture
    (R4, G4, B4, GND) instead of direct 3-bit capture.
    Key insight: 32-bit autopush ÷ 4 bits/pixel = 8 pixels (perfect alignment)
    GPIO 5 (tied to ground) provides free dummy bit for alignment!
    Changes:
    - Updated main.c extraction code for 4-bit capture
2025-11-29 Add session summary: 4-bit RGB capture breakthrough
    Detailed documentation of:
    - The 3-bit problem (10.67 pixel misalignment)
    - The 4-bit solution (perfect 8 pixel alignment)
    - Why only divisors of 32 work with PIO autopush
    - Performance metrics and lessons learned
2025-11-29 Refactor sync detection code
2025-11-30 frame counter over usb
2025-11-30 Update docs for 240p@60fps milestone
2025-11-30 Rename files
2025-12-01 Update documents
2025-12-06 Distorted i2s audio
2025-12-07 grok analysis
2025-12-14 LCD tests
2025-12-15 wip protoboard
2025-12-16 Update docs with correct DVI pin configuration
    - Add DVI_PIN_TESTING.md documenting RP2350 PIO/PWM constraints
    - Update PROJECT_STATUS.md with correct GPIO pinout
    - Update agent instructions with current hardware configuration
2025-12-16 Distorted audio test
2025-12-17 Better sound
2025-12-18 Even better audio, intro voice broken.
2025-12-18 Perfect (?) audio
2025-12-19 480p cap
2025-12-19 480p + single tone audio
2025-12-19 Wait for capture
2025-12-19 Add filters to main firmware
2025-12-20 Document audio noise findings, add IT6615E docs
2025-12-21 Update sch
2025-12-21 Fix submodules and add clone instructions
2025-12-22 Update prototype sch
2025-12-28 Update pins
2025-12-28 First pass cleanup
2025-12-28 Fix Cursor imports
2025-12-28 Code refactor
2025-12-28 Refacor pins mapping
2025-12-28 linter
2025-12-28 Update schematics
2025-12-29 references modulues
2025-12-29 Starting PCB
2026-01-01 GP25+ video capture working
2026-01-02 Disable debug flag.
2026-01-02 Remove old docs
2026-01-02 Update agents
2026-01-02 HSTX is part of the same build
2026-01-02 Move files around
2026-01-02 colored bg
2026-01-02 moar colors
2026-01-02 Move HSTX to core 1
2026-01-02 Clean up
2026-01-03 Wip audio cap to HSTX
2026-01-03 VIDEO AND AUDIO VIA HSTX!!!
2026-01-03 doc cleanup
2026-01-03 Format
2026-01-03 remove rainbow bg
2026-01-03 Remove outdated documentation links from README
    Removed links to PIO Bank 1 Findings and PCB Design Guide.
2026-01-03 DARK and SHADOW support
2026-01-03 more stable init
2026-01-05 Fix video pins mapping
2026-01-06 add osd file
2026-01-07 add osd files
2026-01-07 Video Refactor
2026-01-07 Remove debug printf
2026-01-07 Remove dup code
2026-01-07 remove references
2026-01-07 Gemini file
2026-01-08 Fix typo
2026-01-08 Git ignore
2026-01-10 Fix HDMI signal timing, polarity and signal integrity for strict receivers
2026-01-10 Add release script
2026-01-10 Grant write permissions to CI for releases
2026-01-10 Optimize CI to avoid double builds on release
2026-01-10 Fix release
2026-01-10 Improve audio hiccup issue
2026-01-10 POC for OSD
2026-01-10 256-line buffer
2026-01-10 Update doc
2026-01-10 toggle osd
2026-01-10 toggle osd pull up
2026-01-10 add dark/shadow back
2026-01-11 V1 PCB
2026-01-13 Update hardware
2026-01-13 lib example
2026-01-14 Use pico_hdmi as submodule
2026-01-25 Enable dark/shadow
2026-02-02 Move OSD and line doubling to video pipeline
2026-02-02 Fix lint
2026-02-03 Fix black levels
2026-02-06 Add Discord badge to README
2026-02-07 Revise status table in README.md
    Updated the status table with additional features and corrected formatting.
2026-02-07 Experimental 240p mode
2026-02-08 Update to the latest pico_hdmi
2026-02-08 Disable vid capture
2026-02-08 Fix scratchy audio by using DROP mode. Interpolation might be okay.
2026-02-08 WIP hardware v2
2026-02-13 Improve audio by adding 2s delay on startup
2026-02-13 Auto-fix pre-commit hooks and auto-publish releases on merge
    - Pre-commit: replace check-only clang-format with in-place fix (`clang-format -i`)
    - CI: auto-publish latest pre-release with changelog on merge to main
2026-02-13 Trigger release build
2026-02-14 Fix audio interface
2026-02-14 Empty OSD, IRQ-based
2026-02-14 Minor optimization
2026-02-15 Fast OSD
2026-02-15 Self-test layout
2026-02-16 Optimize video pipeline
2026-02-16 Update the scratchbook
2026-02-16 safe check
2026-02-16 Add missing signal from selftest
2026-02-16 Fix selftest when no csync
2026-02-16 Remove series termination recommendation for PCLK and BCK
    Removed recommendation for series termination resistors.
2026-02-16 Reduce dalay
2026-02-18 Add flag-gated timing experiments and OSD baseline telemetry
2026-02-19 Add DARK test
2026-02-19 Fix OSD postioning
2026-02-20 Opmitize dark/shadow processing
2026-02-20 Fix formatting
2026-02-24 Hardware updates
2026-02-28 Update genlock doc
2026-03-01 Hardware - add HDMI termination resistors and more
2026-03-01 Minor hardware tweaks
2026-03-07 Update FPC 20
2026-03-07 Revert pico_hdmi to 5d8acde
    aa3e245 (via 246fd32) introduced signal instability.
2026-03-08 Add GND plane
2026-03-14 Fix release job: rename output dir to avoid conflict with release script
2026-03-14 Add PCM1802 ADC audio support for AES/non-MV1C boards
    Adds compile-time flag NEOPICO_AUDIO_PCM1802 to build firmware with
    standard I2S capture from an external PCM1802 ADC (12.288MHz SCKI,
    48kHz output). Supports Neo Geo AES and MVS revisions without
    digital audio tap points.
    - New PIO program for standard I2S (1-bit delay, WS LOW=Left, 24-bit)
    - Conditional sample extraction (L/R order, 24→16 bit truncation)
2026-03-24 Fix 240p mode
2026-03-24 Adjust 240p build
2026-03-24 Disable auto release on CI
2026-03-31 Update pico_hdmi dep. Test FW for genlock
2026-03-31 Revert "Update pico_hdmi dep. Test FW for genlock"
    This reverts commit 2d5f67b8291dbe916845bece7cf142347b513a05.
2026-04-24 Update pico_hdmi to 385e954 (adds 720p60 rt-path support)
2026-04-24 Add experimental 720p video mode
2026-04-25 Add stable 720p non-RT build
2026-04-26 Document Samsung 720p game mode investigation
2026-04-26 Remove old kicad project
2026-04-26 Fix OSD build
2026-04-26 Add reboot-based HDMI mode switching
2026-04-27 Stabilize reboot OSD mode switching
    - add flag-gated OSD/audio timing isolation paths
    - pre-render selector UI and keep cold apply path in SRAM
    - fix no-720p reboot callback to render 240p with quad scaling
    - update pico_hdmi submodule for 240p AVI metadata
2026-06-11 Upgrade pico_hdmi to 2.0-beta (7fa6dd5)
    Behaviorally inert: all 2.0 mechanisms (precomposed scanout, native pixel
    mode, ISR-side audio pacing, resync control) are opt-in and OFF. Included
    for free: audio underruns no longer assert the IEC block-start flag (sink
    channel-status resync glitch). The two formerly submodule-only commits
    (240p AVI metadata, reboot-mode switching) are now part of upstream
    2.0-beta, fixing the dangling submodule pointer for fresh clones.
2026-06-11 Add experimental pico_hdmi 2.0 precomposed/native scanout path (480p)
    NEOPICO_EXP_PRECOMPOSED_HDMI (OFF by default; requires NEOPICO_USE_NONRT_HDMI,
    480p-only): pointer-model scanline callback -- video rows return the captured
    line_ring line directly (zero copy; bus replication + HSTX expander do the 2x
    doubling), letterbox/no-signal rows return static native color lines, OSD rows
    compose into a per-line ping/pong native scratch (word loops only in ISR
    context; cache invalidated per frame). Audio islands are patched into
2026-06-12 Add STATE.md live handoff doc; record baseline verdict (docs only)
2026-06-12 CI: drop pico-retrodigital from the KiBot matrix (files no longer in repo)
    Fixes the fabrication job failure (Schematic file not found), which hard-
    blocks the tag release job via needs: [build, fabrication].
2026-06-12 Execute from RAM (copy_to_ram): structural fix for XIP-induced sync drops
    Root cause of months of 'dead code perturbs sync' phenomena and the rare
    20-60 min sync drops in OSD-compiled precomposed builds: XIP flash-fetch
    stalls landing on timing-critical instants, with per-build flash layout
    deciding where they land. Proven by a one-variable oracle: the exact
    394-line patch that glitched instantly from flash runs calm from RAM;
    a build containing every previously-fatal ingredient (precomposed + OSD
2026-06-12 CI: copy_to_ram ONLY for the precomposed variant; RT variants back to flash
    Bisect verdict: RT path + copy_to_ram drops sync within seconds (RT from
    flash is fine; precomposed from RAM is fine for hours). The RT copy-model
    ISR + its DMA feeds have no timing margin for the extra striped-SRAM
    fetch contention that moving all code into RAM creates. v0.7.1's default
    artifacts shipped with this combination and are superseded.
2026-06-12 STATE: ratify Scenario B (precomposed architecture into runtime-modes path)
2026-06-12 Root menu: screen-gate the selftest 1 Hz redraw (icons bled onto the root screen)
    The sampling block was gated on MENU_SCREEN_SELFTEST but the separate 1 Hz
    update block only checked osd_visible, so the spinner and status icons
    kept redrawing over the root menu after returning from Self Test.
2026-06-15 Baseline: single resolution-selector firmware (240p/480p/720p in OSD)
    The selector is now the default build: REBOOT_MODE_SWITCH(+720P) default ON,
    so one firmware switches all three modes from the OSD resolution menu (reboot
    based). CI ships a single neopico_hd.uf2; the 3 fixed-res artifacts are dropped.
    480p now runs at 252 MHz (SYS_CLK_480P_KHZ) for scanline-IRQ headroom: at
    126 MHz its line-doubled 31.5 kHz IRQ left only ~4000 cyc/line and underran
    -> desync. 252 MHz doubles that to ~8000 (matching 240p/720p). pico_hdmi's
2026-06-15 Bump lib/pico_hdmi to f8034c7 (Tier-1 per-scanline ISR trim)
    Gates the perf probe off by default, replaces the v_scanline modulo with
    compare-and-reset, and precomputes the vertical region boundaries -- ~45-70
    cyc/line off the scanline ISR. Behaviorally identical; no clock change.
2026-06-15 Add compile-time audio volume (NEOPICO_AUDIO_VOLUME_PCT, default 100)
    Q15 attenuation on the final SRC output samples (audio_pipeline.c), applied
    only when != 100 so the default build is byte-identical. Attenuation-only ->
    overflow-safe, no clamp. Default 100 = unity (loud-audio turned out to be a
    sink/analog-chain issue, not firmware); knob kept dormant for convenience.
2026-06-15 Flash-backed settings: persist resolution across power-off
    New src/settings.{c,h}: a magic+version+CRC record in the last 4 KB flash
    sector (16 MB part, top sector never collides with the ~75 KB image). Read at
    cold boot, written at the reboot point. Payload has reserved bytes to grow
    without a format bump.
    - request_reboot_mode() persists the selected resolution (blocking erase+program
    before watchdog_reboot; with copy_to_ram the XIP suspend stalls nothing, and
2026-06-15 SCRATCHBOOK: log flash settings + perf/audio session decisions
2026-06-15 SCRATCHBOOK: log resolution-confirm safety net + watchdog-scratch gotcha
2026-06-15 docs: add 720p purple-scanline glitch investigation tracker
    Root-caused to Core 0 capture activity (not channel/content, not FIFO
    underrun). Living document: isolation ladder, FIFO-probe result, ruled-out
    list, mechanism, open tiebreaker experiment, and mitigation options.
2026-06-15 docs(720p glitch): add Game Mode finding (only unbuffered/direct sinks expose it)
2026-06-16 720p: label experimental in OSD + capture-health diag counters + tracker
    - OSD resolution menu: 720p now shows "Experimental (3x)" (rare Game-Mode
    glitch under investigation; see docs/720P_PURPLE_GLITCH.md).
    - NEOPICO_DIAG_COUNTERS (flag-gated, OFF by default): line-ring readiness/
    overrun, capture sync-reset, and in/out frame-rate counters over USB-serial.
    No effect on default builds.
    - OSD_BOOT_OPEN now also works without genlock (boots onto Self Test) for diag.
2026-06-27 audio: recover I2S capture after flashcart resets
